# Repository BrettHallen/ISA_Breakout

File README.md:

# ISA Backplane Boards

## [ISA Penta Backplane](/ISA_Penta)
An attempt at a simple, five-slot ISA board mainly aimed at getting the [Multitech MPF-PC/500 CPU card](https://github.com/BrettHallen/MicroProfessor/tree/main/MPF-PC500) working.<br>

The Multitech card has no documentation (that I've been able to find) and apparently is designed for a "custom" ISA backplane.<br>

## ISA Breakout Board for Logic Analysers
Breakout board to simplify connecting an ISA card to a logic analyser.<br>

Thus I thought it might be useful to have an ISA backplane with all of the signals broken out to pin headers.<br>

This particular design only provides for +5VDC as that appears to be all that the Multitech CPU card requires - the -5V and ±12V pins are not connected.<br>

I've also included a 2x31 pin header (2mm pin pitch) to connect to the ISA backplane designed for the Book 8088 computer so that additional cards, like video & storage, might be added.<br>

## ISA Breakout Card for Logic Analysers
Planning to design an ISA card with pin headers for connection to a logic analyser.

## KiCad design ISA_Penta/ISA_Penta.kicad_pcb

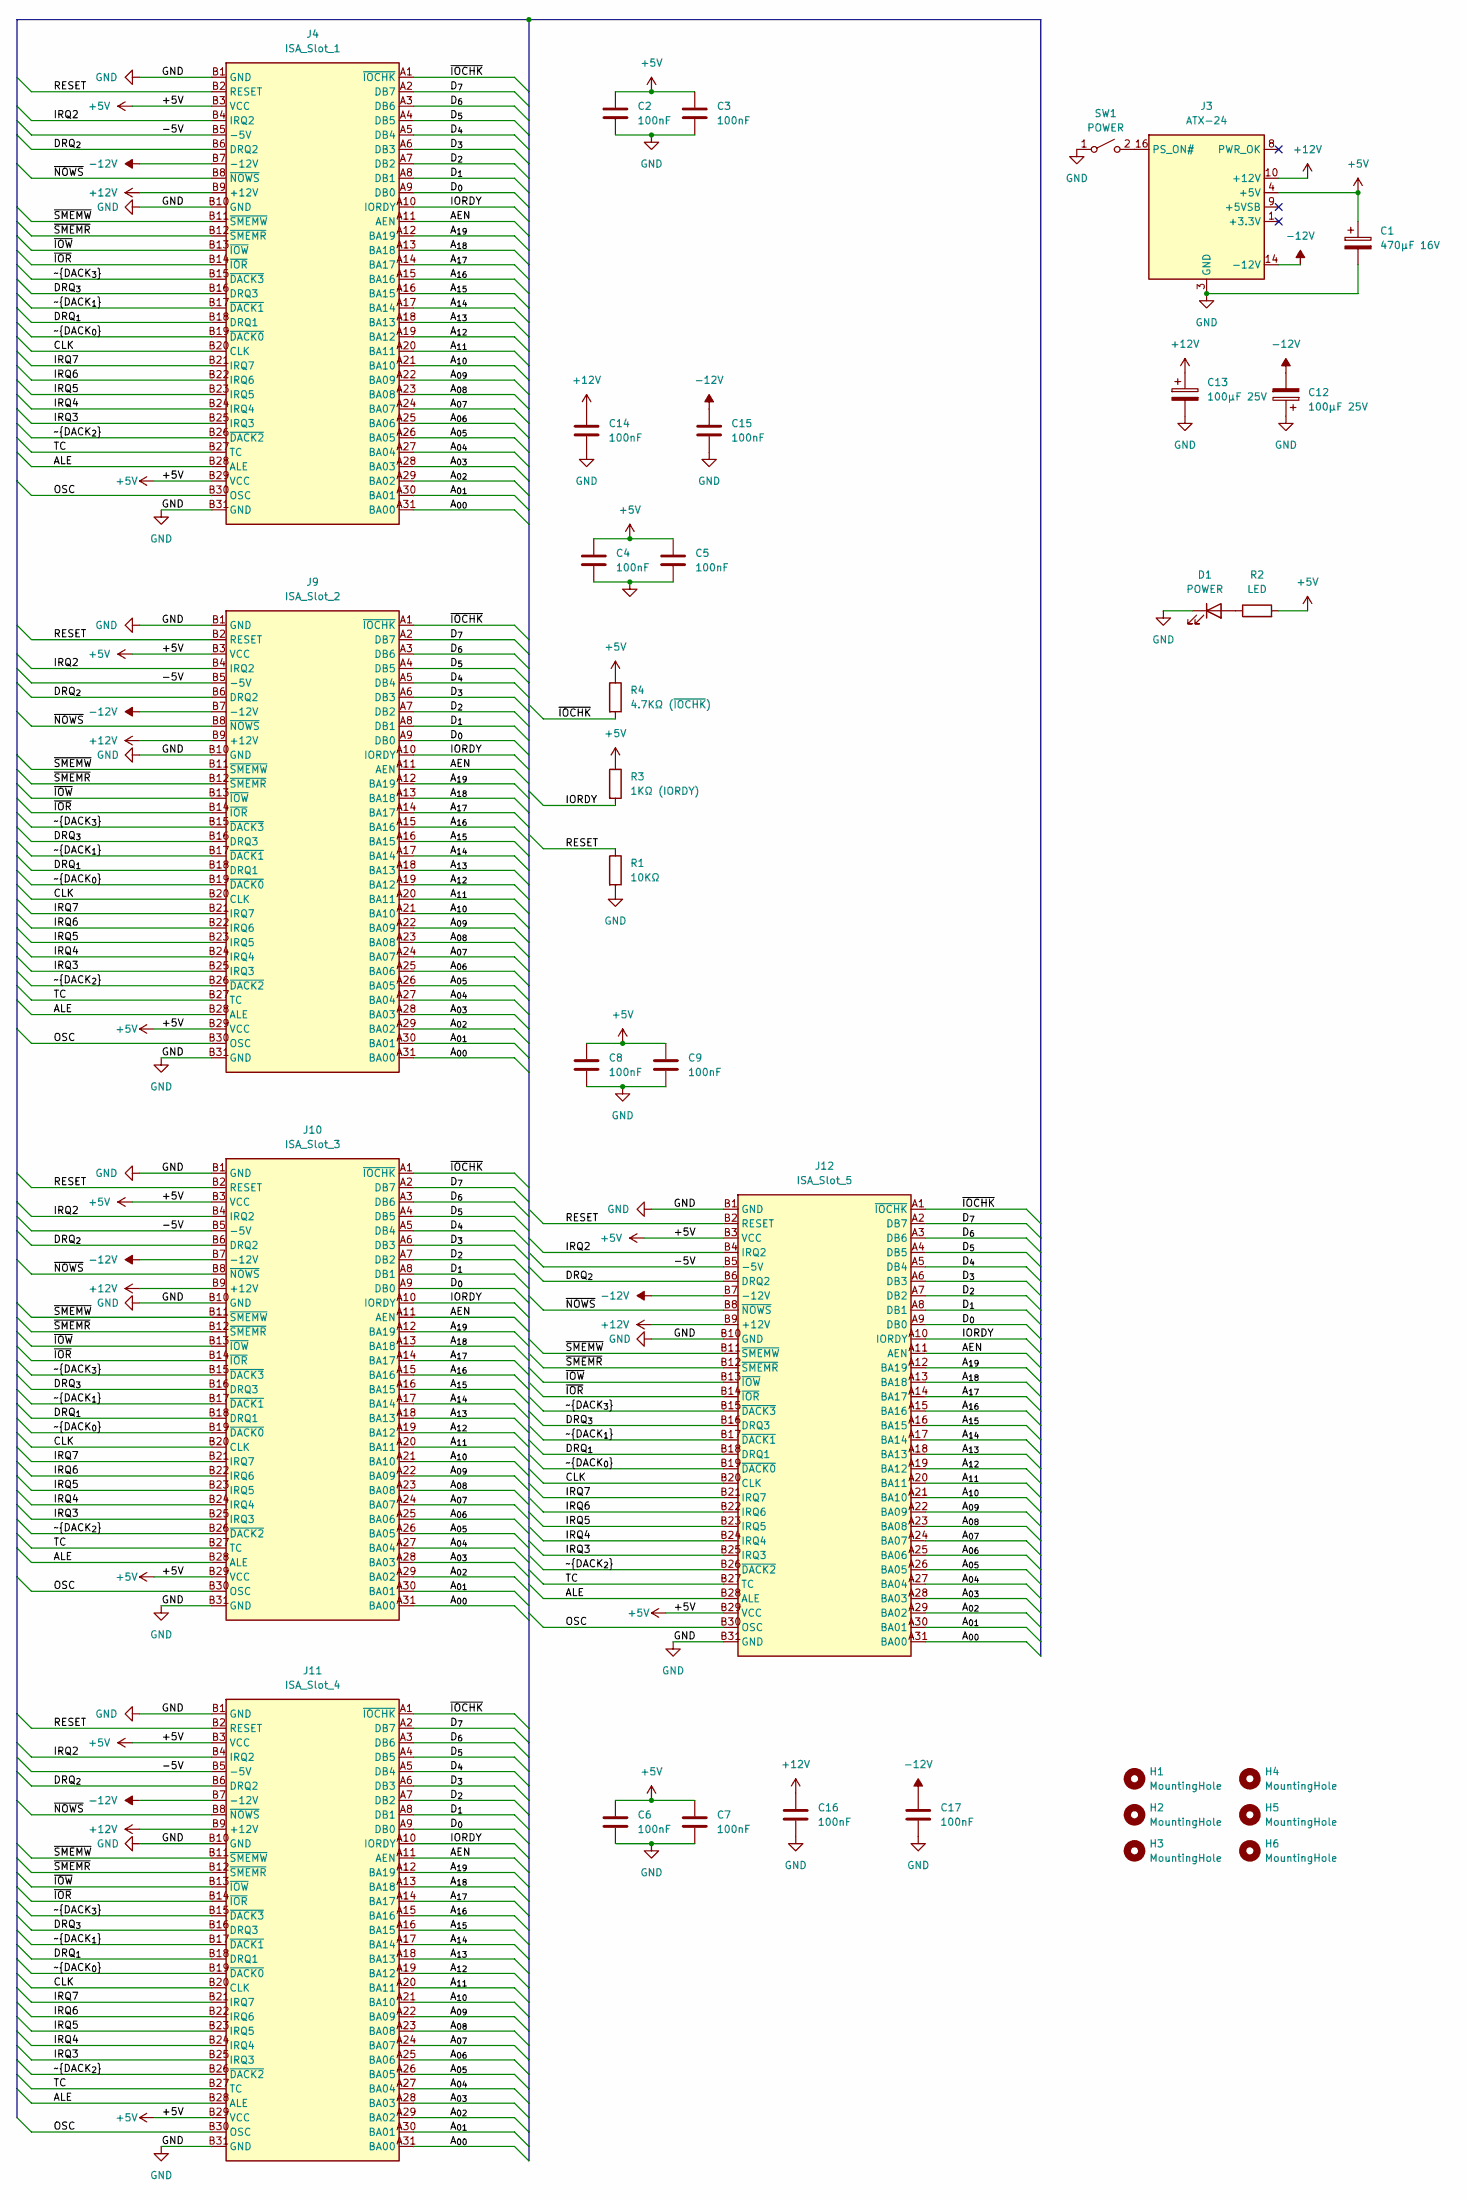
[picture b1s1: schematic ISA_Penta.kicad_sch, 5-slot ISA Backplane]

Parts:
C1: 470µF 16V; CP_Radial_D10.0mm_P5.00mm
C2, C3, C4, C5, C6, C7, C8, C9, C14, C15, C16, C17: 100nF; C_Disc_D3.0mm_W2.0mm_P2.50mm
C12, C13: 100µF 25V; CP_Radial_D5.0mm_P2.50mm
D1: POWER; LED_D5.0mm
H1, H2, H3, H4, H5, H6: MountingHole; MountingHole_3.2mm_M3_DIN965
J3: ATX-24; Molex_Mini-Fit_Jr_5566-24A_2x12_P4.20mm_Vertical
J4: ISA_Slot_1; ISA_8bit_Slot
J9: ISA_Slot_2; ISA_8bit_Slot
J10: ISA_Slot_3; ISA_8bit_Slot
J11: ISA_Slot_4; ISA_8bit_Slot
J12: ISA_Slot_5; ISA_8bit_Slot
R1: 10KΩ; R_Axial_DIN0207_L6.3mm_D2.5mm_P7.62mm_Horizontal
R2: LED; R_Axial_DIN0207_L6.3mm_D2.5mm_P7.62mm_Horizontal
R3: 1KΩ (IORDY); R_Axial_DIN0207_L6.3mm_D2.5mm_P7.62mm_Horizontal
R4: 4.7KΩ (~{IOCHK}); R_Axial_DIN0207_L6.3mm_D2.5mm_P7.62mm_Horizontal
SW1: POWER; PinHeader_1x02_P2.54mm_Vertical

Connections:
+5V: C1.1, C2.1, C3.1, C4.1, C5.1, C6.1, C7.1, C8.1, C9.1, J3.4 (+5V), J3.6 (+5V), J3.21 (+5V), J3.22 (+5V), J3.23 (+5V), J4.B3 (VCC), J4.B29 (VCC), J9.B3 (VCC), J9.B29 (VCC), J10.B3 (VCC), J10.B29 (VCC), J11.B3 (VCC), J11.B29 (VCC), J12.B3 (VCC), J12.B29 (VCC), R2.2, R3.1, R4.1
+12V: C13.1, C14.1, C16.1, J3.10 (+12V), J3.11 (+12V), J4.B9 (+12V), J9.B9 (+12V), J10.B9 (+12V), J11.B9 (+12V), J12.B9 (+12V)
-12V: C12.2, C15.1, C17.1, J3.14 (-12V), J4.B7 (-12V), J9.B7 (-12V), J10.B7 (-12V), J11.B7 (-12V), J12.B7 (-12V)
/-5V: J4.B5 (-5V), J9.B5 (-5V), J10.B5 (-5V), J11.B5 (-5V), J12.B5 (-5V)
/AEN: J4.A11 (AEN), J9.A11 (AEN), J10.A11 (AEN), J11.A11 (AEN), J12.A11 (AEN)
/ALE: J4.B28 (ALE), J9.B28 (ALE), J10.B28 (ALE), J11.B28 (ALE), J12.B28 (ALE)
/A_{00}: J4.A31 (BA00), J9.A31 (BA00), J10.A31 (BA00), J11.A31 (BA00), J12.A31 (BA00)
/A_{01}: J4.A30 (BA01), J9.A30 (BA01), J10.A30 (BA01), J11.A30 (BA01), J12.A30 (BA01)
/A_{02}: J4.A29 (BA02), J9.A29 (BA02), J10.A29 (BA02), J11.A29 (BA02), J12.A29 (BA02)
/A_{03}: J4.A28 (BA03), J9.A28 (BA03), J10.A28 (BA03), J11.A28 (BA03), J12.A28 (BA03)
/A_{04}: J4.A27 (BA04), J9.A27 (BA04), J10.A27 (BA04), J11.A27 (BA04), J12.A27 (BA04)
/A_{05}: J4.A26 (BA05), J9.A26 (BA05), J10.A26 (BA05), J11.A26 (BA05), J12.A26 (BA05)
/A_{06}: J4.A25 (BA06), J9.A25 (BA06), J10.A25 (BA06), J11.A25 (BA06), J12.A25 (BA06)
/A_{07}: J4.A24 (BA07), J9.A24 (BA07), J10.A24 (BA07), J11.A24 (BA07), J12.A24 (BA07)
/A_{08}: J4.A23 (BA08), J9.A23 (BA08), J10.A23 (BA08), J11.A23 (BA08), J12.A23 (BA08)
/A_{09}: J4.A22 (BA09), J9.A22 (BA09), J10.A22 (BA09), J11.A22 (BA09), J12.A22 (BA09)
/A_{10}: J4.A21 (BA10), J9.A21 (BA10), J10.A21 (BA10), J11.A21 (BA10), J12.A21 (BA10)
/A_{11}: J4.A20 (BA11), J9.A20 (BA11), J10.A20 (BA11), J11.A20 (BA11), J12.A20 (BA11)
/A_{12}: J4.A19 (BA12), J9.A19 (BA12), J10.A19 (BA12), J11.A19 (BA12), J12.A19 (BA12)
/A_{13}: J4.A18 (BA13), J9.A18 (BA13), J10.A18 (BA13), J11.A18 (BA13), J12.A18 (BA13)
/A_{14}: J4.A17 (BA14), J9.A17 (BA14), J10.A17 (BA14), J11.A17 (BA14), J12.A17 (BA14)
/A_{15}: J4.A16 (BA15), J9.A16 (BA15), J10.A16 (BA15), J11.A16 (BA15), J12.A16 (BA15)
/A_{16}: J4.A15 (BA16), J9.A15 (BA16), J10.A15 (BA16), J11.A15 (BA16), J12.A15 (BA16)
/A_{17}: J4.A14 (BA17), J9.A14 (BA17), J10.A14 (BA17), J11.A14 (BA17), J12.A14 (BA17)
/A_{18}: J4.A13 (BA18), J9.A13 (BA18), J10.A13 (BA18), J11.A13 (BA18), J12.A13 (BA18)
/A_{19}: J4.A12 (BA19), J9.A12 (BA19), J10.A12 (BA19), J11.A12 (BA19), J12.A12 (BA19)
/CLK: J4.B20 (CLK), J9.B20 (CLK), J10.B20 (CLK), J11.B20 (CLK), J12.B20 (CLK)
/DRQ_{1}: J4.B18 (DRQ1), J9.B18 (DRQ1), J10.B18 (DRQ1), J11.B18 (DRQ1), J12.B18 (DRQ1)
/DRQ_{2}: J4.B6 (DRQ2), J9.B6 (DRQ2), J10.B6 (DRQ2), J11.B6 (DRQ2), J12.B6 (DRQ2)
/DRQ_{3}: J4.B16 (DRQ3), J9.B16 (DRQ3), J10.B16 (DRQ3), J11.B16 (DRQ3), J12.B16 (DRQ3)
/D_{0}: J4.A9 (DB0), J9.A9 (DB0), J10.A9 (DB0), J11.A9 (DB0), J12.A9 (DB0)
/D_{1}: J4.A8 (DB1), J9.A8 (DB1), J10.A8 (DB1), J11.A8 (DB1), J12.A8 (DB1)
/D_{2}: J4.A7 (DB2), J9.A7 (DB2), J10.A7 (DB2), J11.A7 (DB2), J12.A7 (DB2)
/D_{3}: J4.A6 (DB3), J9.A6 (DB3), J10.A6 (DB3), J11.A6 (DB3), J12.A6 (DB3)
/D_{4}: J4.A5 (DB4), J9.A5 (DB4), J10.A5 (DB4), J11.A5 (DB4), J12.A5 (DB4)
/D_{5}: J4.A4 (DB5), J9.A4 (DB5), J10.A4 (DB5), J11.A4 (DB5), J12.A4 (DB5)
/D_{6}: J4.A3 (DB6), J9.A3 (DB6), J10.A3 (DB6), J11.A3 (DB6), J12.A3 (DB6)
/D_{7}: J4.A2 (DB7), J9.A2 (DB7), J10.A2 (DB7), J11.A2 (DB7), J12.A2 (DB7)
/IORDY: J4.A10 (IORDY), J9.A10 (IORDY), J10.A10 (IORDY), J11.A10 (IORDY), J12.A10 (IORDY), R3.2
/IRQ2: J4.B4 (IRQ2), J9.B4 (IRQ2), J10.B4 (IRQ2), J11.B4 (IRQ2), J12.B4 (IRQ2)
/IRQ3: J4.B25 (IRQ3), J9.B25 (IRQ3), J10.B25 (IRQ3), J11.B25 (IRQ3), J12.B25 (IRQ3)
/IRQ4: J4.B24 (IRQ4), J9.B24 (IRQ4), J10.B24 (IRQ4), J11.B24 (IRQ4), J12.B24 (IRQ4)
/IRQ5: J4.B23 (IRQ5), J9.B23 (IRQ5), J10.B23 (IRQ5), J11.B23 (IRQ5), J12.B23 (IRQ5)
/IRQ6: J4.B22 (IRQ6), J9.B22 (IRQ6), J10.B22 (IRQ6), J11.B22 (IRQ6), J12.B22 (IRQ6)
/IRQ7: J4.B21 (IRQ7), J9.B21 (IRQ7), J10.B21 (IRQ7), J11.B21 (IRQ7), J12.B21 (IRQ7)
/OSC: J4.B30 (OSC), J9.B30 (OSC), J10.B30 (OSC), J11.B30 (OSC), J12.B30 (OSC)
/RESET: J4.B2 (RESET), J9.B2 (RESET), J10.B2 (RESET), J11.B2 (RESET), J12.B2 (RESET), R1.1
/TC: J4.B27 (TC), J9.B27 (TC), J10.B27 (TC), J11.B27 (TC), J12.B27 (TC)
/~DACK_{0}: J4.B19 (~DACK0), J9.B19 (~DACK0), J10.B19 (~DACK0), J11.B19 (~DACK0), J12.B19 (~DACK0)
/~DACK_{1}: J4.B17 (~DACK1), J9.B17 (~DACK1), J10.B17 (~DACK1), J11.B17 (~DACK1), J12.B17 (~DACK1)
/~DACK_{2}: J4.B26 (~DACK2), J9.B26 (~DACK2), J10.B26 (~DACK2), J11.B26 (~DACK2), J12.B26 (~DACK2)
/~DACK_{3}: J4.B15 (~DACK3), J9.B15 (~DACK3), J10.B15 (~DACK3), J11.B15 (~DACK3), J12.B15 (~DACK3)
/~IOCHK: J4.A1 (~IOCHK), J9.A1 (~IOCHK), J10.A1 (~IOCHK), J11.A1 (~IOCHK), J12.A1 (~IOCHK), R4.2
/~IOR: J4.B14 (~IOR), J9.B14 (~IOR), J10.B14 (~IOR), J11.B14 (~IOR), J12.B14 (~IOR)
/~IOW: J4.B13 (~IOW), J9.B13 (~IOW), J10.B13 (~IOW), J11.B13 (~IOW), J12.B13 (~IOW)
/~NOWS: J4.B8 (~NOWS), J9.B8 (~NOWS), J10.B8 (~NOWS), J11.B8 (~NOWS), J12.B8 (~NOWS)
/~SMEMR: J4.B12 (~SMEMR), J9.B12 (~SMEMR), J10.B12 (~SMEMR), J11.B12 (~SMEMR), J12.B12 (~SMEMR)
/~SMEMW: J4.B11 (~SMEMW), J9.B11 (~SMEMW), J10.B11 (~SMEMW), J11.B11 (~SMEMW), J12.B11 (~SMEMW)
GND: C1.2, C2.2, C3.2, C4.2, C5.2, C6.2, C7.2, C8.2, C9.2, C12.1, C13.2, C14.2, C15.2, C16.2, C17.2, D1.1 (K), J3.3 (GND), J3.5 (GND), J3.7 (GND), J3.15 (GND), J3.17 (GND), J3.18 (GND), J3.19 (GND), J3.24 (GND), J4.B1 (GND), J4.B10 (GND), J4.B31 (GND), J9.B1 (GND), J9.B10 (GND), J9.B31 (GND), J10.B1 (GND), J10.B10 (GND), J10.B31 (GND), J11.B1 (GND), J11.B10 (GND), J11.B31 (GND), J12.B1 (GND), J12.B10 (GND), J12.B31 (GND), R1.2, SW1.1 (A)
unnamed: D1.2 (A), R2.1
unnamed: J3.16 (PS_ON#), SW1.2 (B)

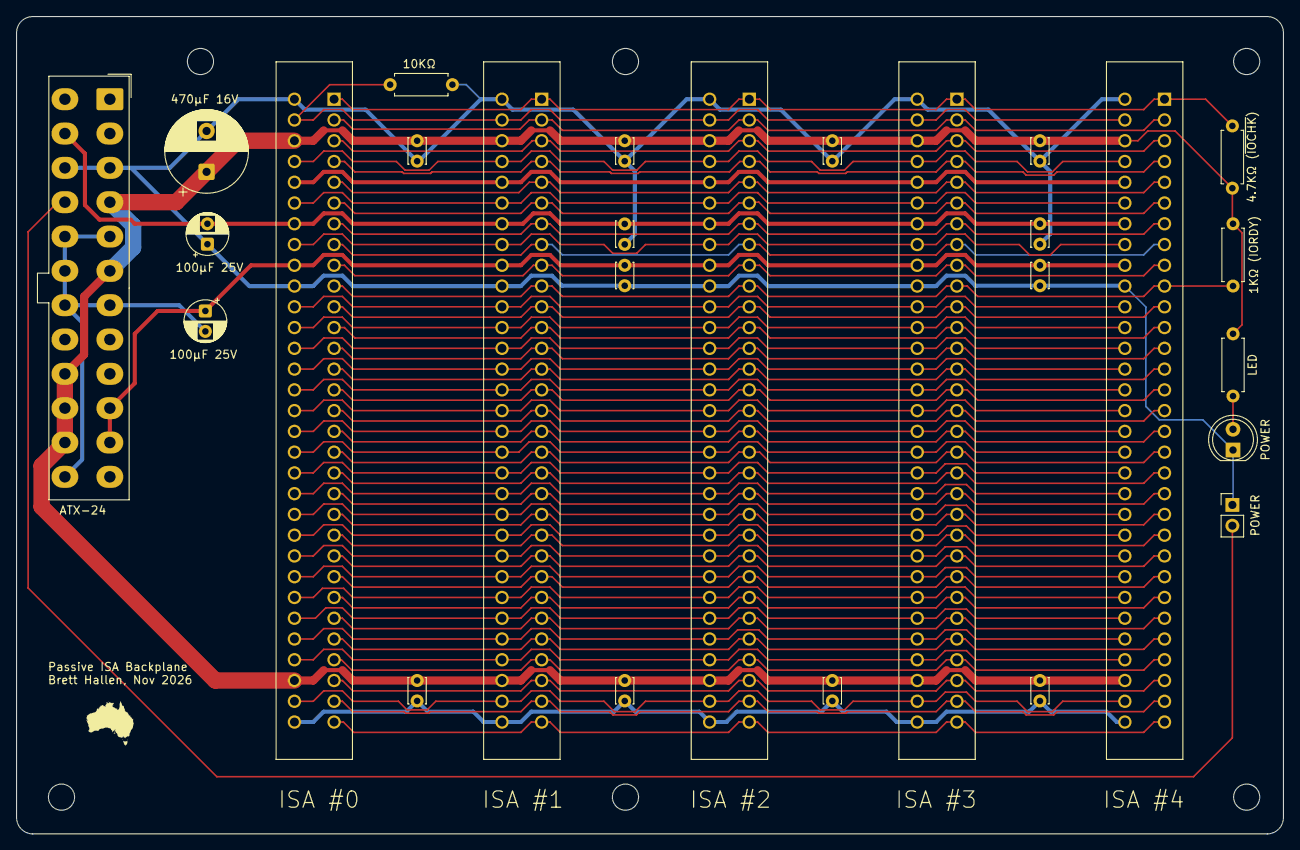
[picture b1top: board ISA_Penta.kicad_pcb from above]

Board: 2 copper layers, 155.0 x 100.0 mm, 33 parts (0 on the bottom side), 61 nets.

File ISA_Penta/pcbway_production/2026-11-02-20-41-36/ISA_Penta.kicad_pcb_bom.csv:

Designator,Quantity,Value,Footprint,Package,MPN,DNP,Mount_Type,Description,KiLib_Generator,Sim.Pins
C1,1,470µF 16V,CP_Radial_D10.0mm_P5.00mm,,,,tht,Polarized capacitor,capacitor/THT/other,
"C12, C13",2,100µF 25V,CP_Radial_D5.0mm_P2.50mm,,,,tht,Polarized capacitor,capacitor/THT/other,
"C14, C15, C16, C17, C2, C3, C4, C5, C6, C7, C8, C9",12,100nF,C_Disc_D3.0mm_W2.0mm_P2.50mm,,,,tht,Unpolarized capacitor,capacitor/THT/other,
D1,1,POWER,LED_D5.0mm,,,,tht,Light emitting diode,LED/THT,1=K 2=A
J10,1,ISA_Slot_3,ISA_8bit_Slot,,,,tht,8-bit ISA-PC bus connector,,
J11,1,ISA_Slot_4,ISA_8bit_Slot,,,,tht,8-bit ISA-PC bus connector,,
J12,1,ISA_Slot_5,ISA_8bit_Slot,,,,tht,8-bit ISA-PC bus connector,,
J3,1,ATX-24,Molex_Mini-Fit_Jr_5566-24A_2x12_P4.20mm_Vertical,,,,tht,ATX Power supply 24pins,connector/Molex,
J4,1,ISA_Slot_1,ISA_8bit_Slot,,,,tht,8-bit ISA-PC bus connector,,
J9,1,ISA_Slot_2,ISA_8bit_Slot,,,,tht,8-bit ISA-PC bus connector,,
R1,1,10KΩ,R_Axial_DIN0207_L6.3mm_D2.5mm_P7.62mm_Horizontal,,,,tht,Resistor,resistor/THT,
R2,1,LED,R_Axial_DIN0207_L6.3mm_D2.5mm_P7.62mm_Horizontal,,,,tht,Resistor,resistor/THT,
R3,1,1KΩ (IORDY),R_Axial_DIN0207_L6.3mm_D2.5mm_P7.62mm_Horizontal,,,,tht,Resistor,resistor/THT,
R4,1,4.7KΩ (~{IOCHK}),R_Axial_DIN0207_L6.3mm_D2.5mm_P7.62mm_Horizontal,,,,tht,Resistor,resistor/THT,
SW1,1,POWER,PinHeader_1x02_P2.54mm_Vertical,,,,tht,Single Pole Single Throw (SPST) switch,connector/pin_header_socket,

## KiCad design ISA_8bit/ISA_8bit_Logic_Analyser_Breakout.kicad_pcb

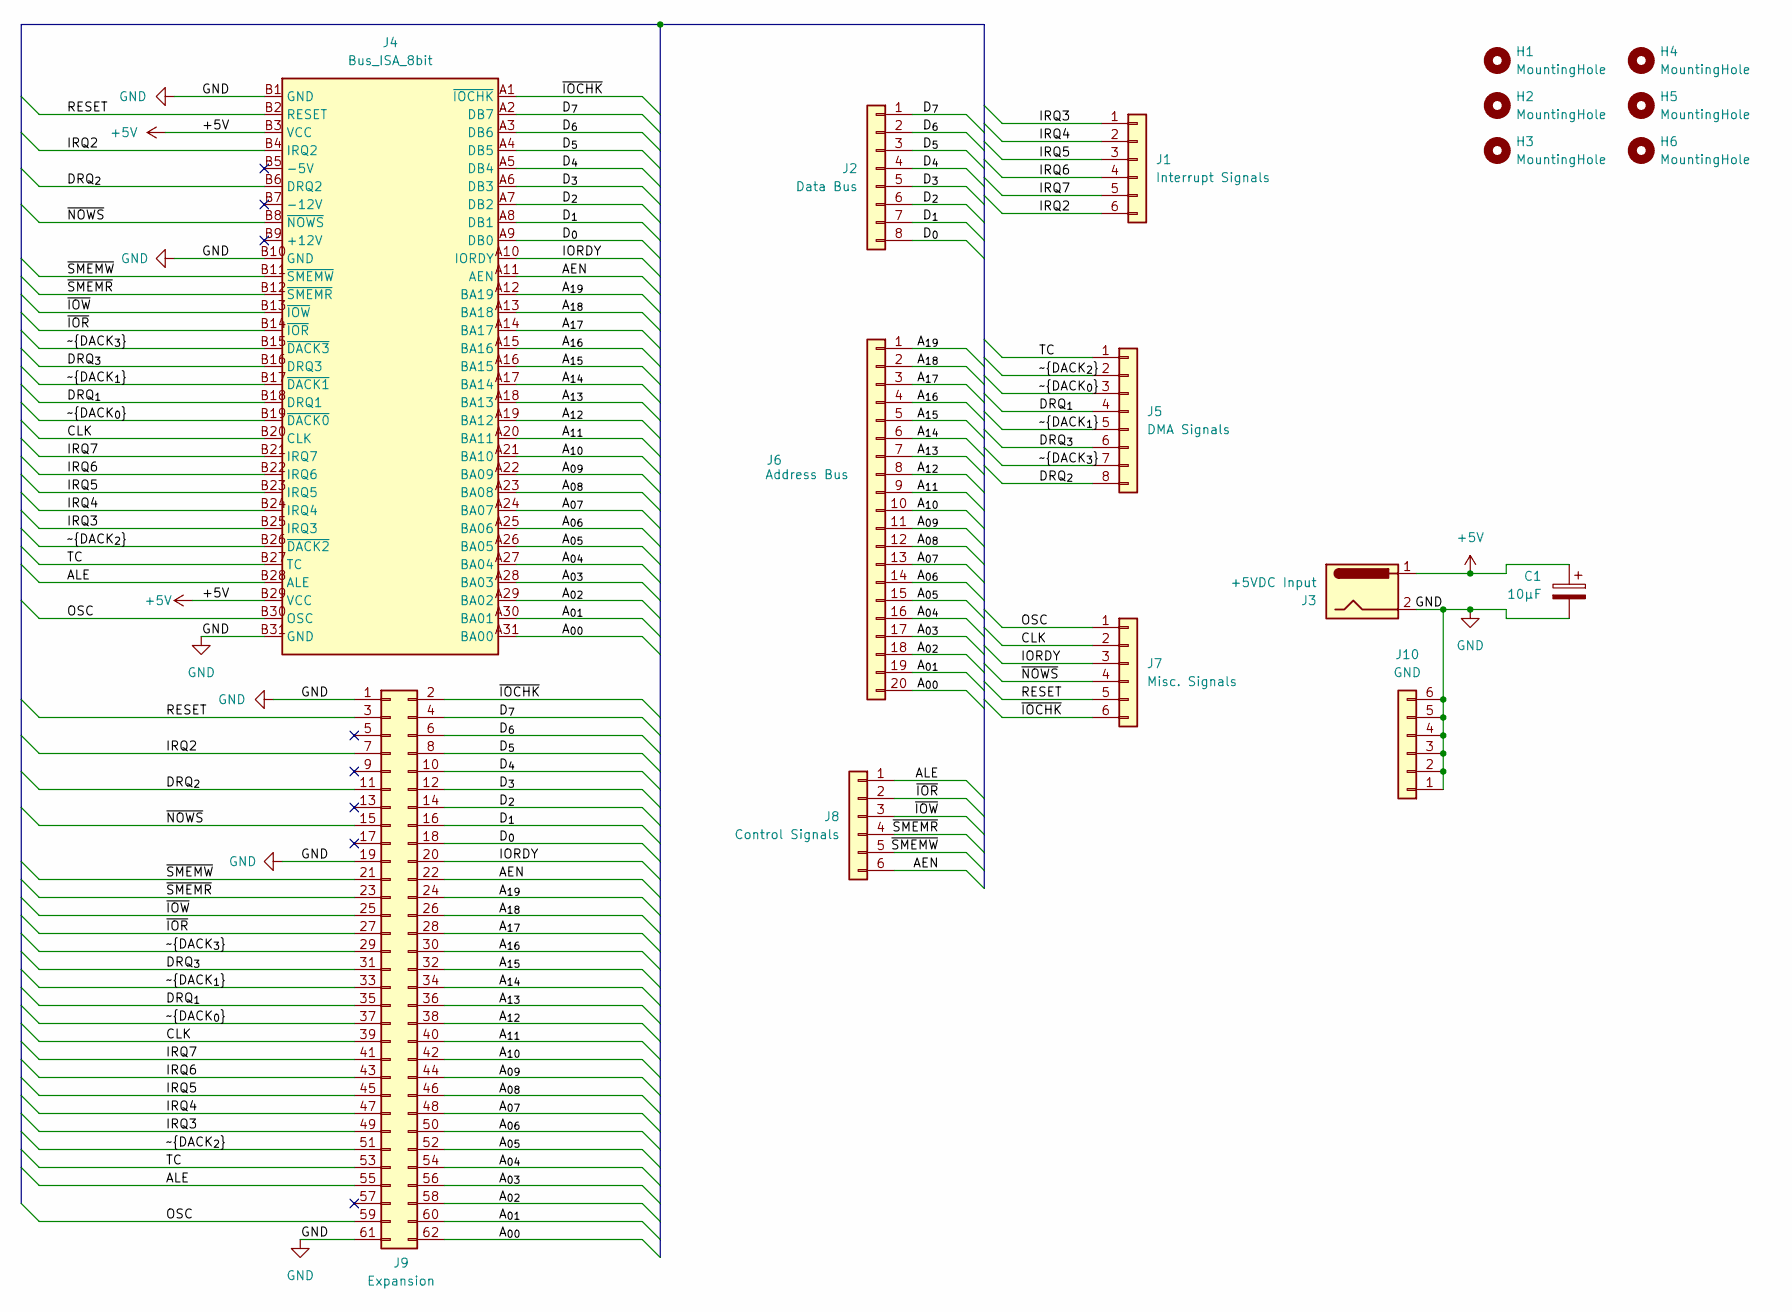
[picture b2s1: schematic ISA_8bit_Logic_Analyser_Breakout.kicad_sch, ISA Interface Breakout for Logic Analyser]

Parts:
C1: 10µF; CP_Radial_D5.0mm_P2.50mm
H1, H2, H3, H4, H5, H6: MountingHole; MountingHole_3.2mm_M3_DIN965
J1: Interrupt Signals; PinHeader_1x06_P2.54mm_Vertical
J2: Data Bus; PinHeader_1x08_P2.54mm_Vertical
J3: +5VDC Input; BarrelJack_Horizontal
J4: Bus_ISA_8bit; ISA_8bit_Slot
J5: DMA Signals; PinHeader_1x08_P2.54mm_Vertical
J6: Address Bus; PinHeader_1x20_P2.54mm_Vertical
J7: Misc. Signals; PinHeader_1x06_P2.54mm_Vertical
J8: Control Signals; PinHeader_1x06_P2.54mm_Vertical
J9: Expansion; PinHeader_2x31_P2.00mm_Vertical
J10: GND; PinHeader_1x06_P2.54mm_Vertical

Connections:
+5V: C1.1, J3.1, J4.B3 (VCC), J4.B29 (VCC)
/AEN: J4.A11 (AEN), J8.6, J9.22
/ALE: J4.B28 (ALE), J8.1, J9.55
/A_{00}: J4.A31 (BA00), J6.20, J9.62
/A_{01}: J4.A30 (BA01), J6.19, J9.60
/A_{02}: J4.A29 (BA02), J6.18, J9.58
/A_{03}: J4.A28 (BA03), J6.17, J9.56
/A_{04}: J4.A27 (BA04), J6.16, J9.54
/A_{05}: J4.A26 (BA05), J6.15, J9.52
/A_{06}: J4.A25 (BA06), J6.14, J9.50
/A_{07}: J4.A24 (BA07), J6.13, J9.48
/A_{08}: J4.A23 (BA08), J6.12, J9.46
/A_{09}: J4.A22 (BA09), J6.11, J9.44
/A_{10}: J4.A21 (BA10), J6.10, J9.42
/A_{11}: J4.A20 (BA11), J6.9, J9.40
/A_{12}: J4.A19 (BA12), J6.8, J9.38
/A_{13}: J4.A18 (BA13), J6.7, J9.36
/A_{14}: J4.A17 (BA14), J6.6, J9.34
/A_{15}: J4.A16 (BA15), J6.5, J9.32
/A_{16}: J4.A15 (BA16), J6.4, J9.30
/A_{17}: J4.A14 (BA17), J6.3, J9.28
/A_{18}: J4.A13 (BA18), J6.2, J9.26
/A_{19}: J4.A12 (BA19), J6.1, J9.24
/CLK: J4.B20 (CLK), J7.2, J9.39
/DRQ_{1}: J4.B18 (DRQ1), J5.4, J9.35
/DRQ_{2}: J4.B6 (DRQ2), J5.8, J9.11
/DRQ_{3}: J4.B16 (DRQ3), J5.6, J9.31
/D_{0}: J2.8, J4.A9 (DB0), J9.18
/D_{1}: J2.7, J4.A8 (DB1), J9.16
/D_{2}: J2.6, J4.A7 (DB2), J9.14
/D_{3}: J2.5, J4.A6 (DB3), J9.12
/D_{4}: J2.4, J4.A5 (DB4), J9.10
/D_{5}: J2.3, J4.A4 (DB5), J9.8
/D_{6}: J2.2, J4.A3 (DB6), J9.6
/D_{7}: J2.1, J4.A2 (DB7), J9.4
/IORDY: J4.A10 (IORDY), J7.3, J9.20
/IRQ2: J1.6, J4.B4 (IRQ2), J9.7
/IRQ3: J1.1, J4.B25 (IRQ3), J9.49
/IRQ4: J1.2, J4.B24 (IRQ4), J9.47
/IRQ5: J1.3, J4.B23 (IRQ5), J9.45
/IRQ6: J1.4, J4.B22 (IRQ6), J9.43
/IRQ7: J1.5, J4.B21 (IRQ7), J9.41
/OSC: J4.B30 (OSC), J7.1, J9.59
/RESET: J4.B2 (RESET), J7.5, J9.3
/TC: J4.B27 (TC), J5.1, J9.53
/~DACK_{0}: J4.B19 (~DACK0), J5.3, J9.37
/~DACK_{1}: J4.B17 (~DACK1), J5.5, J9.33
/~DACK_{2}: J4.B26 (~DACK2), J5.2, J9.51
/~DACK_{3}: J4.B15 (~DACK3), J5.7, J9.29
/~IOCHK: J4.A1 (~IOCHK), J7.6, J9.2
/~IOR: J4.B14 (~IOR), J8.2, J9.27
/~IOW: J4.B13 (~IOW), J8.3, J9.25
/~NOWS: J4.B8 (~NOWS), J7.4, J9.15
/~SMEMR: J4.B12 (~SMEMR), J8.4, J9.23
/~SMEMW: J4.B11 (~SMEMW), J8.5, J9.21
GND: C1.2, J3.2, J4.B1 (GND), J4.B10 (GND), J4.B31 (GND), J9.1, J9.19, J9.61, J10.1, J10.2, J10.3, J10.4, J10.5, J10.6

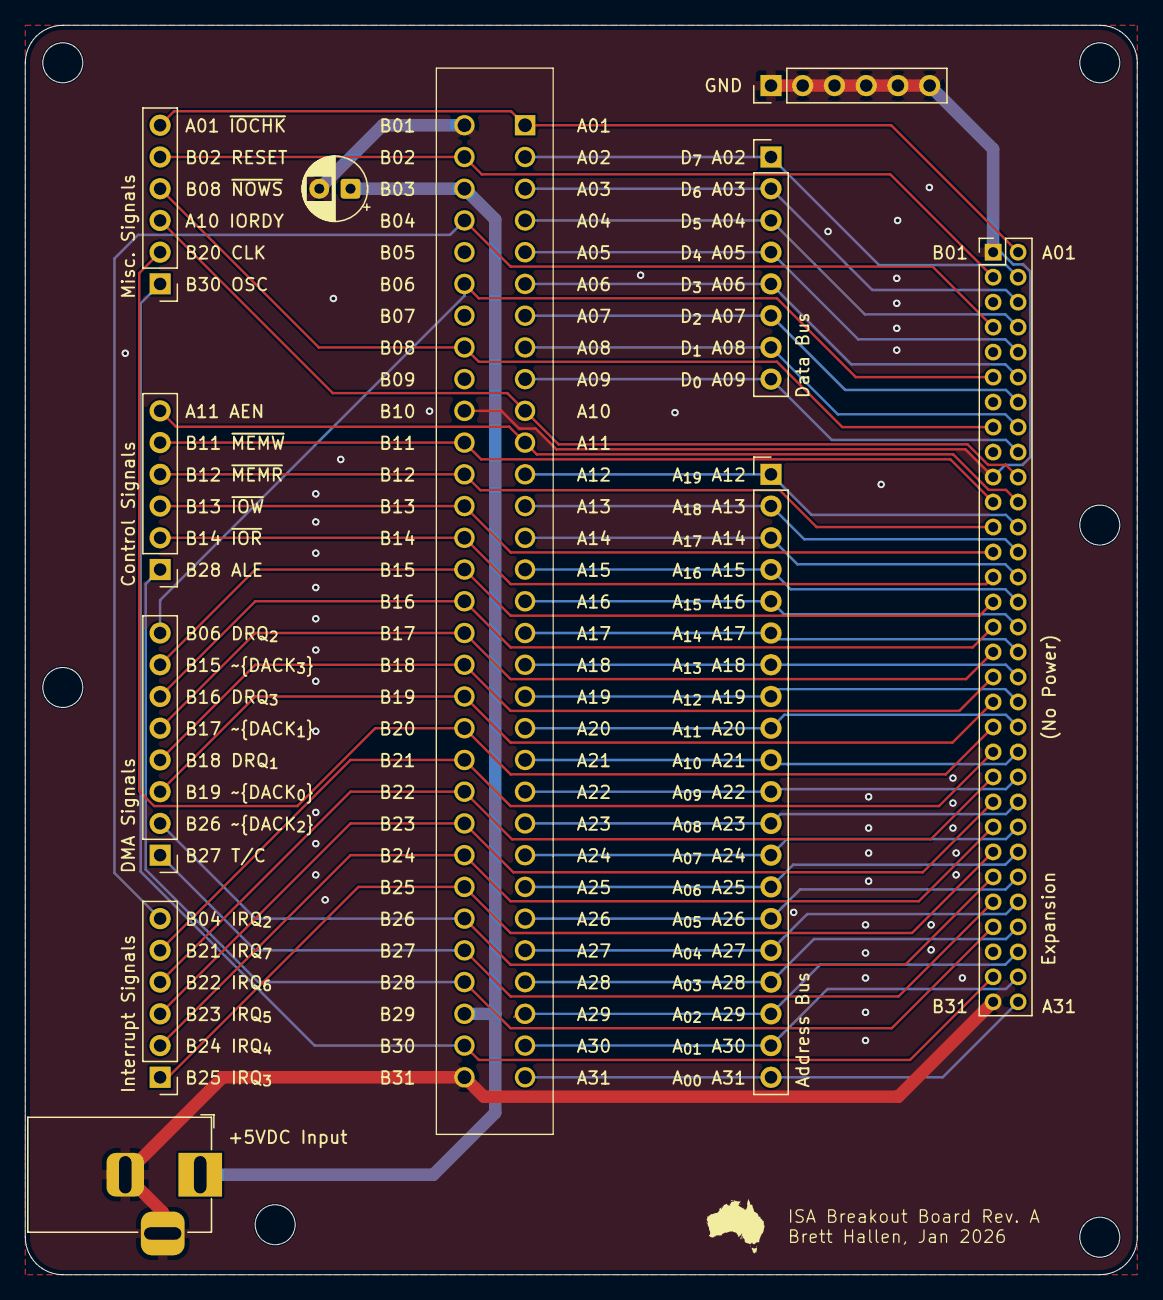
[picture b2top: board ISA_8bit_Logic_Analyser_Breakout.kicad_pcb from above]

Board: 2 copper layers, 89.0 x 100.0 mm, 17 parts (0 on the bottom side), 56 nets.

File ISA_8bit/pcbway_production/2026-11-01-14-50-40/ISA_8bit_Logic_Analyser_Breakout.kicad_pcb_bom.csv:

Designator,Quantity,Value,Footprint,Package,MPN,DNP,Mount_Type,Description
C1,1,10µF,CP_Radial_D5.0mm_P2.50mm,,,,tht,Polarized capacitor
J1,1,Interrupt Signals,PinHeader_1x06_P2.54mm_Vertical,,,,tht,"Generic connector, single row, 01x06, script generated (kicad-library-utils/schlib/autogen/connector/)"
J10,1,GND,PinHeader_1x06_P2.54mm_Vertical,,,,tht,"Generic connector, single row, 01x06, script generated (kicad-library-utils/schlib/autogen/connector/)"
J2,1,Data Bus,PinHeader_1x08_P2.54mm_Vertical,,,,tht,"Generic connector, single row, 01x08, script generated (kicad-library-utils/schlib/autogen/connector/)"
J3,1,+5VDC Input,BarrelJack_Horizontal,,,,tht,DC Barrel Jack
J4,1,Bus_ISA_8bit,ISA_8bit_Slot,,,,tht,8-bit ISA-PC bus connector
J5,1,DMA Signals,PinHeader_1x08_P2.54mm_Vertical,,,,tht,"Generic connector, single row, 01x08, script generated (kicad-library-utils/schlib/autogen/connector/)"
J6,1,Address Bus,PinHeader_1x20_P2.54mm_Vertical,,,,tht,"Generic connector, single row, 01x20, script generated (kicad-library-utils/schlib/autogen/connector/)"
J7,1,Misc. Signals,PinHeader_1x06_P2.54mm_Vertical,,,,tht,"Generic connector, single row, 01x06, script generated (kicad-library-utils/schlib/autogen/connector/)"
J8,1,Control Signals,PinHeader_1x06_P2.54mm_Vertical,,,,tht,"Generic connector, single row, 01x06, script generated (kicad-library-utils/schlib/autogen/connector/)"
J9,1,Expansion,PinHeader_2x31_P2.00mm_Vertical,,,,tht,"Generic connector, double row, 02x31, odd/even pin numbering scheme (row 1 odd numbers, row 2 even numbers), script generated (kicad-library-utils/schlib/autogen/connector/)"
